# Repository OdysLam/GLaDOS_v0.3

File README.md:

# GLaDOS_v0.3
The 3rd version of glados smart home system.

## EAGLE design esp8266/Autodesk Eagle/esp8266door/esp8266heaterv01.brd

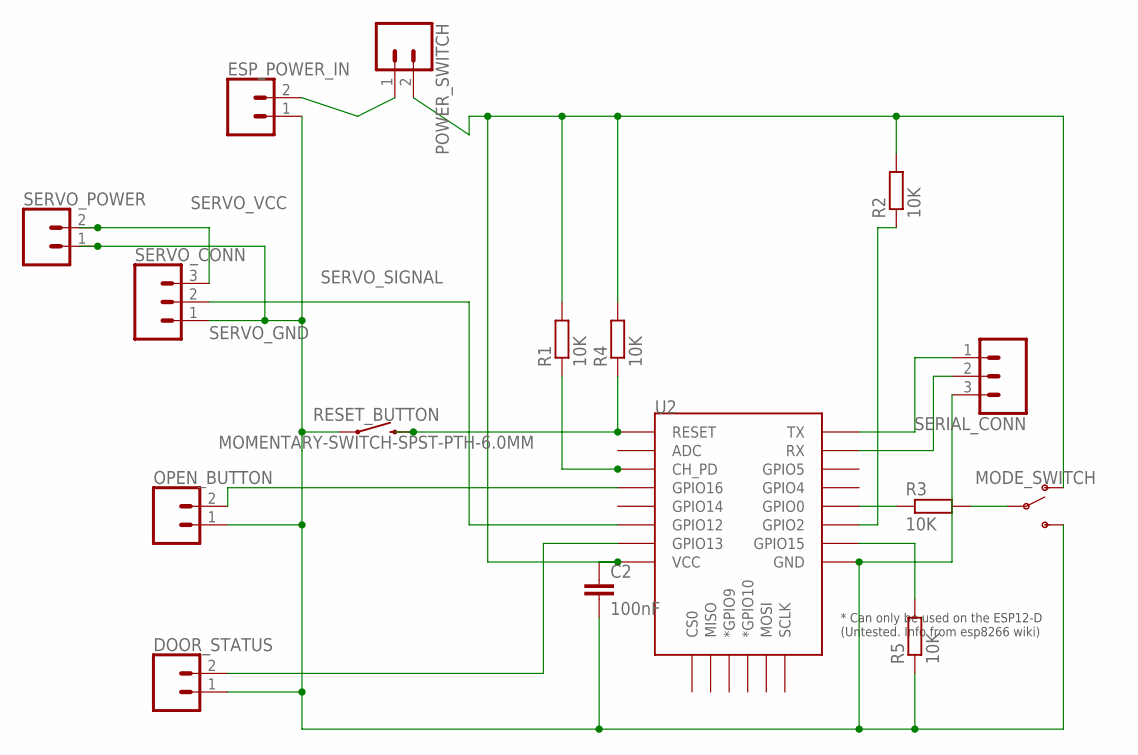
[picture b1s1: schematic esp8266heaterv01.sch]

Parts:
C2: 100nF; C025-024X044
DOOR_STATUS: CONN_02-JST-2-PTH-NO_SILK; JST-2-PTH-NS
ESP_POWER_IN: CONN_02JST-PTH-2; JST-2-PTH
MODE_SWITCH: SWITCH-SPDT-PTH-11.6X4.0MM; SWITCH_SPDT_PTH_11.6X4.0MM
OPEN_BUTTON: CONN_02-JST-2-PTH-NO_SILK; JST-2-PTH-NS
POWER_SWITCH: CONN_02-JST-2-PTH-NO_SILK; JST-2-PTH-NS
R1, R2, R3, R4, R5: 10K; 0204/7
RESET_BUTTON: MOMENTARY-SWITCH-SPST-PTH-6.0MM; TACTILE_SWITCH_PTH_6.0MM
SERIAL_CONN: CONN_03POGO_PIN_HOLES_ONLY; 1X03_PP_HOLES_ONLY
SERVO_CONN: CONN_03; 1X03
SERVO_POWER: CONN_02JST-PTH-2; JST-2-PTH
U2: ESP12ESMD; ESP12E-SMD

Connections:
unnamed: C2.1, MODE_SWITCH.1 (O), POWER_SWITCH.2, R1.2, R2.2, R4.2, U2.VCC
unnamed: OPEN_BUTTON.2, U2.GPIO16
unnamed: R3.1, U2.GPIO0
unnamed: R4.1, RESET_BUTTON.3 (2), U2.RESET
unnamed: R1.1, U2.CH_PD
unnamed: R5.2, U2.GPIO15
unnamed: MODE_SWITCH.2, R3.2
unnamed: SERIAL_CONN.1, U2.TXD0 (TX)
unnamed: SERIAL_CONN.2, U2.RXD0 (RX)
unnamed: DOOR_STATUS.2, U2.GPIO13
unnamed: R2.1, U2.GPIO2
unnamed: ESP_POWER_IN.2, POWER_SWITCH.1
unnamed: C2.2, DOOR_STATUS.1, MODE_SWITCH.3 (S), OPEN_BUTTON.1, R5.1, SERIAL_CONN.3, U2.GND
SERVO_GND: ESP_POWER_IN.1, RESET_BUTTON.1, SERVO_CONN.1, SERVO_POWER.1
SERVO_SIGNAL: SERVO_CONN.2, U2.GPIO12
SERVO_VCC: SERVO_CONN.3, SERVO_POWER.2

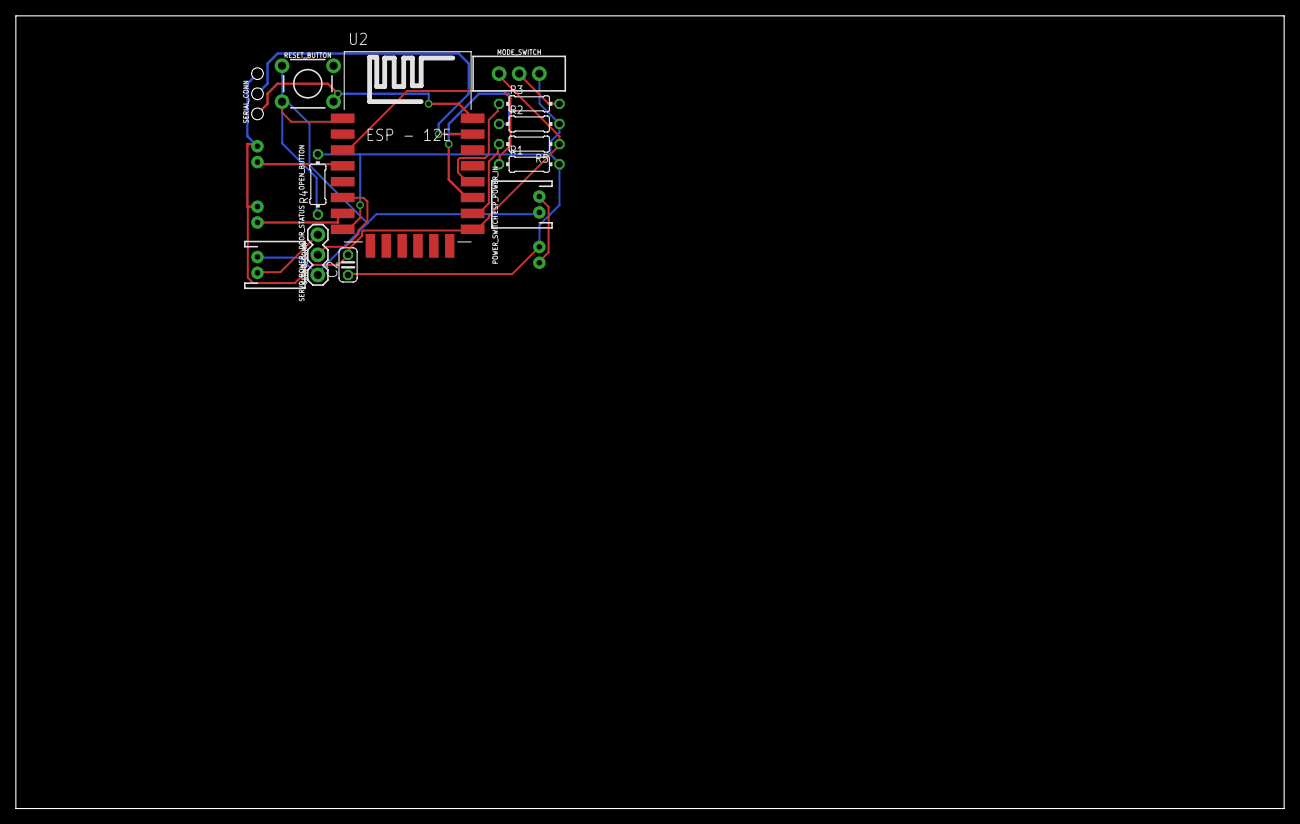
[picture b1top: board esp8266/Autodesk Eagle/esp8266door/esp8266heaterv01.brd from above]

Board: 2 copper layers, 160.0 x 100.0 mm, 16 parts (0 on the bottom side), 16 nets.

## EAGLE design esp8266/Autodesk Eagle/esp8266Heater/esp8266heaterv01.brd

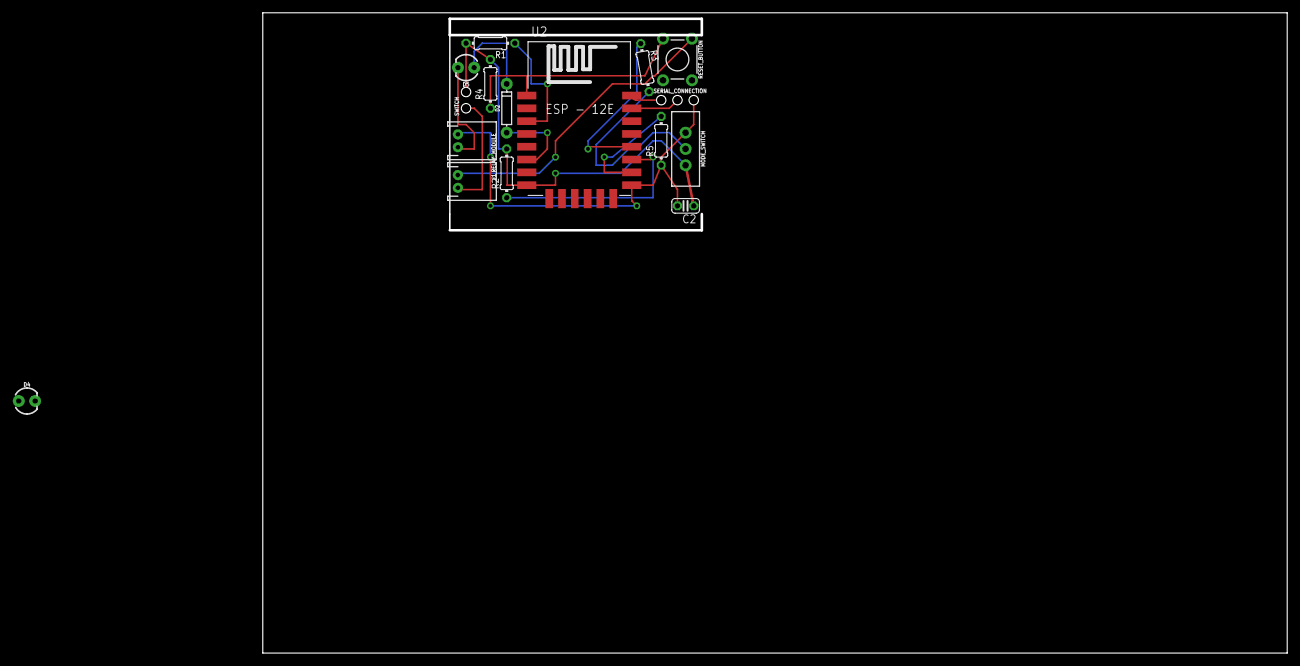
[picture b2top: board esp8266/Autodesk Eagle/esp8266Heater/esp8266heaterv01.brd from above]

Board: 2 copper layers, 160.0 x 100.0 mm, 16 parts (0 on the bottom side), 15 nets.

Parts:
C2: 100nF; C025-024X044
D2: 200mA/100V/1V; DIODE-1N4148
D4, D5: LED_3MM
J1: Power; JST-2-PTH
MODE_SWITCH: SWITCH_SPDT_PTH_11.6X4.0MM
R1, R2, R3, R4, R5: 10K; 0204/7
RELAY_MODULE: JST-2-PTH
RESET_BUTTON: MOMENTARY-SWITCH-SPST-PTH-6.0MM; TACTILE_SWITCH_PTH_6.0MM
SERIAL_CONNECTION: 1X03_PP_HOLES_ONLY
SWITCH: 1X02_PP_HOLES_ONLY
U2: ESP12E-SMD

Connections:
unnamed: C2.1, MODE_SWITCH.1, R1.2, R2.2, R4.2, SWITCH.2, U2.VCC
unnamed: D5.K, RELAY_MODULE.2
unnamed: R3.1, U2.GPIO0
unnamed: R4.1, RESET_BUTTON.3, U2.RESET
unnamed: R1.1, U2.CH_PD
unnamed: R5.2, U2.GPIO15
unnamed: MODE_SWITCH.2, R3.2
unnamed: SERIAL_CONNECTION.1, U2.TXD0
unnamed: SERIAL_CONNECTION.2, U2.RXD0
unnamed: D2.A, U2.GPIO12
unnamed: R2.1, U2.GPIO2
unnamed: J1.1, RESET_BUTTON.1
unnamed: J1.2, SWITCH.1
unnamed: D2.C, D5.A
unnamed: C2.2, MODE_SWITCH.3, R5.1, RELAY_MODULE.1, SERIAL_CONNECTION.3, U2.GND

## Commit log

2017-09-05 added gitignore
2017-09-05 initial push
2017-09-05 clear

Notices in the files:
parts and their libraries:
SparkFun-DiscreteSemi: Licensing: Creative Commons ShareAlike 4.0 International - https://creativecommons.org/licenses/by-sa/4.0
